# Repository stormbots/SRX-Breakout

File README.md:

# Talon SRX Breakouts
Breakout circuit boards for easier wiring with the Talon SRX motor controller.

All source files are created using [CADSoft Eagle](http://www.cadsoftusa.com/download-eagle/). They can be uploaded by downloading the BRD files, and uploading them to a PCB fabrication service such as [OSHPark.com](http://oshpark.com)

- [SRX Dataport Breakout](SRX_Dataport_Breakout/): Provides a simple breakout to 0.1" servo headers for simpler wiring of inputs
   
- [SRX CAN Plugboard](SRX_CAN_Plugboard/): Provides a spring plug for the SRX for connecting to the CAN network, similar to the other 2015 control system devices.

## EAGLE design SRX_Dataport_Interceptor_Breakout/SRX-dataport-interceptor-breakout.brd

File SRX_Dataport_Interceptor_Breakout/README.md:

# Talon SRX Dataport Intercepter Breakout
This board breaks out the Talon SRX pins into a more easily usable 3-wire configuration that's compatible with standard servo cabling. This variant also includes a passthrough to the Gadgeteer port, allowing mixed usage of both 3 wire and Gadgeteer plug devices from [CTRE](http://www.ctr-electronics.com/). 

For additional configuration of the Talon SRX to take advantage of this board, see the [Talon SRX User's guide](http://content.vexrobotics.com/vexpro/pdf/Talon-SRX-User-Guide-20150201.pdf)

## Wiring
 The 4 3-wire connectors simply match servo cable order. Since switches generally don't care about voltage, all 3-wire signals use 3.3V. The voltage for the Analog Input Signal pin MUST be 3.3V in order to avoid damage to the Talon SRX.
 
 Connection Name | Pin 1 | Pin 2 | Pin 3 
 ---|---|---|---
Forward Limit Switch | GND |3.3V| Signal
Reverse Limit Switch | GND |3.3V| Signal
Quadrature Index Switch | GND |3.3V| Signal
Analog Input | GND |3.3V| Signal

The 4 wire quadrature encoder has a slightly different configuration. In addition, a solder jumper on the reverse side of the board allows for a configurable voltage. This is needed since some encoder boards require 5V signals, rather than the 3.3V.

Connection Name | Pin 1 | Pin 2 | Pin 3 |Pin 4
---|---|---|---|---
 Quadrature Encoder |GND | 3.3V or 5V |Signal A | Signal B

### Gadgeteer Pin Usage Chart
The Gadgeteer passthrough port works exactly as the one on the SRX does, with the same pinout and shroud orientation. 
Note, that compatibility issues will arise if both the Gadgeteer device and 3 wire device try to drive the same input line. This is called [bus contention](https://google.com/search?q=bus contention) and can result in incorrect operation or damage to your devices. 

This is not guaranteed to be complete, but may help assess what pins are available in combination with various other devices

Component                   |Analog |Fwd Limit| Rev Limit |Quad A | Quad B|
----------------------------|:-----:|:-------:|:---------:|:-----:|:-----:|
[CTRE Mag Encoder](http://www.ctr-electronics.com/srx-magnetic-encoder.html) |   Used   |         |           |  Used    |   Used   

[mag]: ""

## Bill Of Materials

Quantity | Description                  | Part Number |link
--------:|-----|------------------------|-------------|---
4        |  3-pin 0.1" header | Generic | [Digikey](http://www.digikey.com/product-detail/en/61300311121/732-5316-ND/4846825)
1        |  4-pin 0.1" header | Generic | [Digikey](http://www.digikey.com/product-detail/en/M20-9990445/952-2265-ND/3728229)
1        |  14-position 0.5" header | FCI 20021321-00014T4LF | [Digikey](https://www.digikey.com/product-detail/en/20021321-00014T4LF/609-3771-ND/2209082)
2        |  10k resistor (0603 package) | Generic | [Digikey](https://www.digikey.com/product-detail/en/RC0603JR-0710KL/311-10KGRCT-ND/729647)
2        |  Jumper wires | Generic 22 gauge wire  | 
1        | 10 pin 0.05" pitch shrouded socket | CNC Tech 3220-10-0100-00| [Digikey](http://www.digikey.com/product-detail/en/3220-10-0100-00/1175-1627-ND/3883661) 

## Assembly
1. Assemble the surface mount components to the bottom of the board
2. Solder the jumper to select the voltage for the quadrature encoder. 
3. Attach the wire jumpers. These jumpers only work as spacers between the Talon SRX and the PCB. This helps stabilize the connector, and prevent shorting against the 0.1" headers.
4. Attach the 0.1" headers so they face away from the body of the Talon SRX
4. Optionally, attach the 0.05" header so they face away from the body of the Talon SRX
5. Place a piece of electrical tape over the bottom of the board, covering the 0.1" headers, resistors, and solder jumpers.

## Mounting 
1. Remove the screws on the Talon SRX
2. Gently connect the backside connector to the Talon SRX. 
3. Re-insert the screws, and tighten gently. Do not use excessive force*

*  _Using significant force on the screws can damage the Talon SRX. It can also cause the 0.1" joints to punch through the electrical tape, causing signal errors or power shorting. The jumper wires will help provide spacing to prevent these issues._

## FRC Technicalities
This is a passive wiring board, and contains no active components.

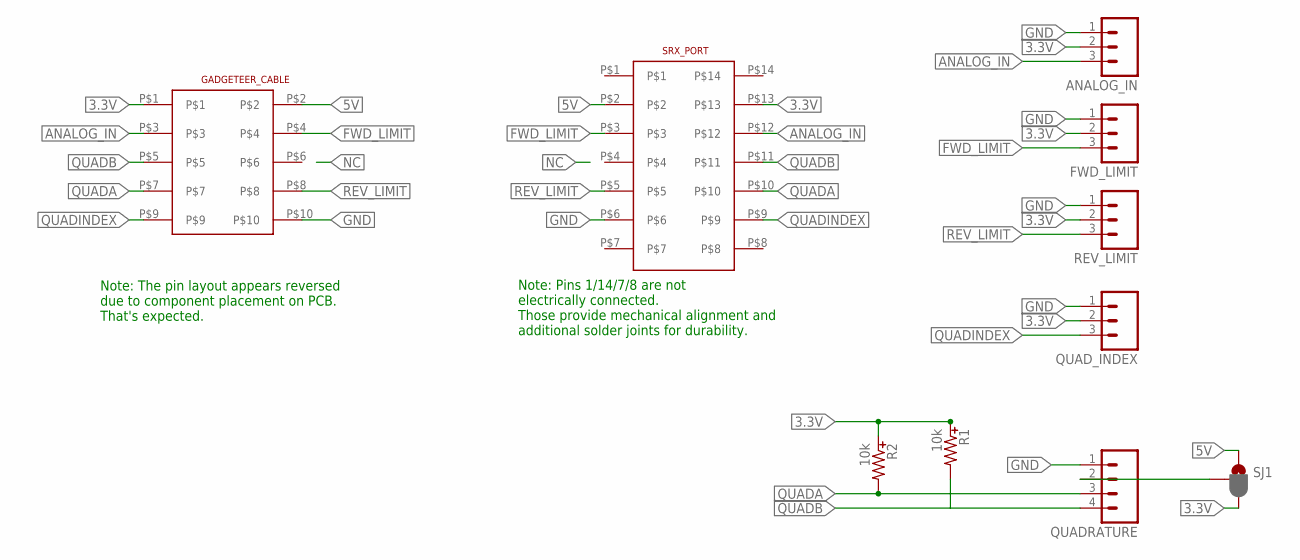
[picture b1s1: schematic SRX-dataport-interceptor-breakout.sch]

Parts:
ANALOG_IN: M03LOCK; 1X03_LOCK
FWD_LIMIT: M03LOCK; 1X03_LOCK
GADGETEER_CABLE: M05X02M_SHROUDED; M2X05_M_SHROUDED
QUADRATURE: M04LOCK; 1X04_LOCK
QUAD_INDEX: M03LOCK; 1X03_LOCK
R1, R2: 10k; 0402-0603-0805-UNIVERSAL
REV_LIMIT: M03LOCK; 1X03_LOCK
SJ1: JUMPER-PAD-3-2OF3_NC_BY_PASTE; PAD-JUMPER-3-2OF3_NC_BY_PASTE_YES_SILK_FULL_BOX
SRX_PORT: M07X0220021321-00014TFLF; M2X07_SMD

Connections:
3.3V: ANALOG_IN.2, FWD_LIMIT.2, GADGETEER_CABLE.P$1, QUAD_INDEX.2, R1.+ (1), R2.+ (1), REV_LIMIT.2, SJ1.3, SRX_PORT.P$13
5V: GADGETEER_CABLE.P$2, SJ1.1, SRX_PORT.P$2
ANALOG_IN: ANALOG_IN.3, GADGETEER_CABLE.P$3, SRX_PORT.P$12
FWD_LIMIT: FWD_LIMIT.3, GADGETEER_CABLE.P$4, SRX_PORT.P$3
GND: ANALOG_IN.1, FWD_LIMIT.1, GADGETEER_CABLE.P$10, QUADRATURE.1, QUAD_INDEX.1, REV_LIMIT.1, SRX_PORT.P$6
QUADA: GADGETEER_CABLE.P$7, QUADRATURE.3, R2.- (2), SRX_PORT.P$10
QUADB: GADGETEER_CABLE.P$5, QUADRATURE.4, R1.- (2), SRX_PORT.P$11
QUADINDEX: GADGETEER_CABLE.P$9, QUAD_INDEX.3, SRX_PORT.P$9
QUAD_VOLTAGE: QUADRATURE.2, SJ1.2
REV_LIMIT: GADGETEER_CABLE.P$8, REV_LIMIT.3, SRX_PORT.P$5

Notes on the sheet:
Note: Pins 1/14/7/8 are not electrically connected. Those provide mechanical alignment and additional solder joints for durability.
Note: The pin layout appears reversed due to component placement on PCB. That's expected.

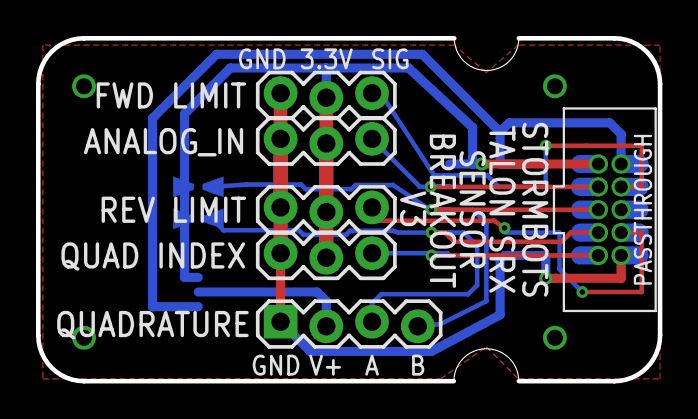
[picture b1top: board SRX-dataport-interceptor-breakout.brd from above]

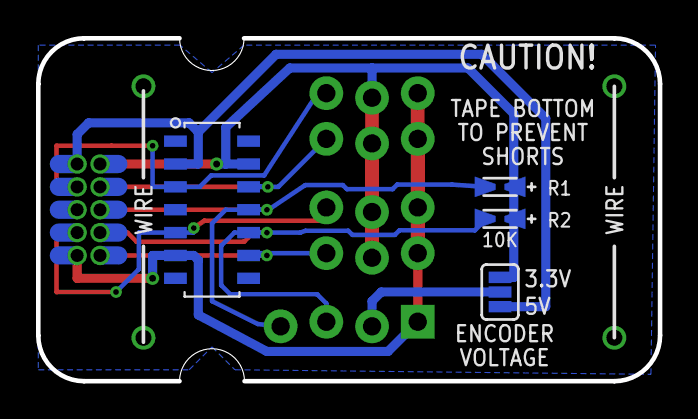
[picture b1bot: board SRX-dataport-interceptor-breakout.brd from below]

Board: 2 copper layers, 34.5 x 19.1 mm, 11 parts (4 on the bottom side), 10 nets.

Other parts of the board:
U$1: TALONSRX

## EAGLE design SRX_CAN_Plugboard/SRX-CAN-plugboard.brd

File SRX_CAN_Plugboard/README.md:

# SRX CAN Plugboard
Provides a spring plug for the SRX for connecting to the CAN network, similar to the other 2015 control system devices. This enables you to cut the wires shorter, and use Ferrule terminators instead of splicing.

## Assembly
No special notes. Simply solder components to the board. 

## Mounting
Can be mounted with either screws or zip ties. Mounting holes and zip tie indents are spaced 1" apart on either side of the connector.

This cannot be mounted directly on conductive surfaces. Doing so will likely short the CAN connections, halting the robot. It's suggested to add a wood block or other spacer when mounting on a surface that may cause the pins to short.

## FRC Technicalities
This is a passive wiring board, and contains no active components.

## Bill Of Materials
Quantity | Description                  | Part Number |link
--------:|-----|------------------------|-------------|---
4        |  2 slot vertical spring mount| Weidmuller 1825960000 | [Digikey](http://www.digikey.com/product-detail/en/1825960000/281-2124-ND/1094462)

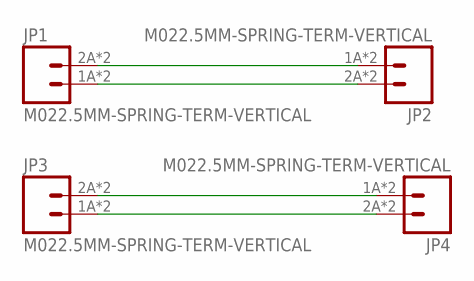
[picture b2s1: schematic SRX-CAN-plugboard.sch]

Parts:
JP1, JP2, JP3, JP4: M022.5MM-SPRING-TERM-VERTICAL; 1824740000-2X-VERTICAL-SPRING-TERMINAL

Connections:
unnamed: JP3.2A (2), JP3.2B (2), JP4.1A (1), JP4.1B (1)
unnamed: JP3.1A (1), JP3.1B (1), JP4.2A (2), JP4.2B (2)
unnamed: JP1.1A (1), JP1.1B (1), JP2.2A (2), JP2.2B (2)
unnamed: JP1.2A (2), JP1.2B (2), JP2.1A (1), JP2.1B (1)

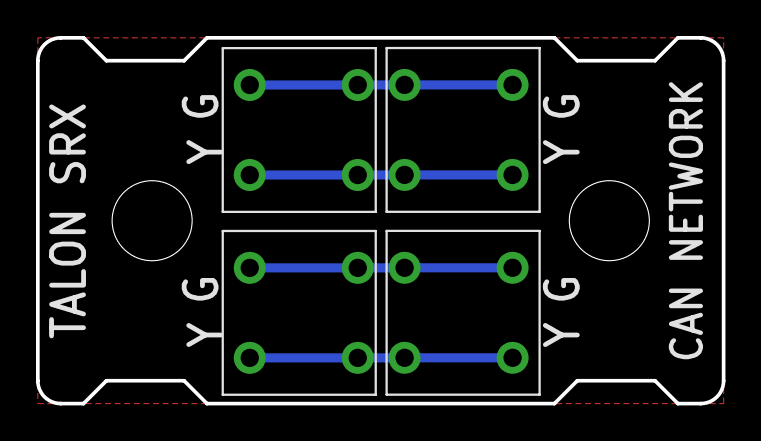
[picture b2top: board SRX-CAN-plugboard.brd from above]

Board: 2 copper layers, 38.1 x 20.3 mm, 4 parts (0 on the bottom side), 4 nets.

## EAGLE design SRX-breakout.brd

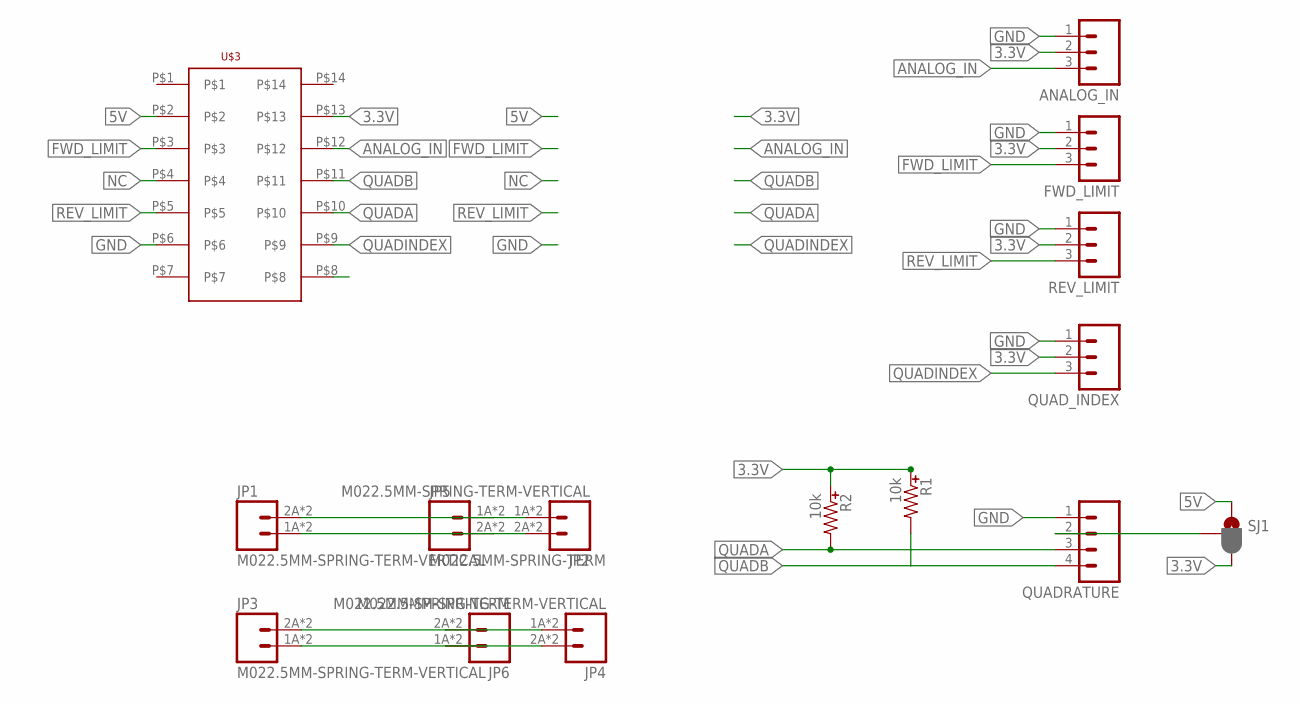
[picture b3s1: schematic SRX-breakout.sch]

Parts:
ANALOG_IN: M03LOCK; 1X03_LOCK
FWD_LIMIT: M03LOCK; 1X03_LOCK
JP1, JP2, JP3, JP4: M022.5MM-SPRING-TERM-VERTICAL; 1824740000-2X-VERTICAL-SPRING-TERMINAL
JP5, JP6: M022.5MM-SPRING-TERM; 1824740000-2X-STRAIGHT-SPRING-TERMINAL
QUADRATURE: M04LOCK; 1X04_LOCK
QUAD_INDEX: M03LOCK; 1X03_LOCK
R1, R2: 10k; 0402-0603-0805-UNIVERSAL
REV_LIMIT: M03LOCK; 1X03_LOCK
SJ1: JUMPER-PAD-3-2OF3_NC_BY_PASTE; PAD-JUMPER-3-2OF3_NC_BY_PASTE_YES_SILK_FULL_BOX
U$3: M07X0220021321-00014TFLF; M2X07_SMD

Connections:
3.3V: ANALOG_IN.2, FWD_LIMIT.2, QUAD_INDEX.2, R1.+ (1), R2.+ (1), REV_LIMIT.2, SJ1.3, U$3.P$13
5V: SJ1.1, U$3.P$2
ANALOG_IN: ANALOG_IN.3, U$3.P$12
FWD_LIMIT: FWD_LIMIT.3, U$3.P$3
GND: ANALOG_IN.1, FWD_LIMIT.1, QUADRATURE.1, QUAD_INDEX.1, REV_LIMIT.1, U$3.P$6
unnamed: JP3.2A (2), JP3.2B (2), JP4.1A (1), JP4.1B (1), JP6.2A (1), JP6.2B (1)
unnamed: JP3.1A (1), JP3.1B (1), JP4.2A (2), JP4.2B (2), JP6.1A (2), JP6.1B (2)
unnamed: JP1.1A (1), JP1.1B (1), JP2.2A (2), JP2.2B (2), JP5.2A (1), JP5.2B (1)
unnamed: JP1.2A (2), JP1.2B (2), JP2.1A (1), JP2.1B (1), JP5.1A (2), JP5.1B (2)
NC: U$3.P$4
QUADA: QUADRATURE.3, R2.- (2), U$3.P$10
QUADB: QUADRATURE.4, R1.- (2), U$3.P$11
QUADINDEX: QUAD_INDEX.3, U$3.P$9
QUAD_VOLTAGE: QUADRATURE.2, SJ1.2
REV_LIMIT: REV_LIMIT.3, U$3.P$5

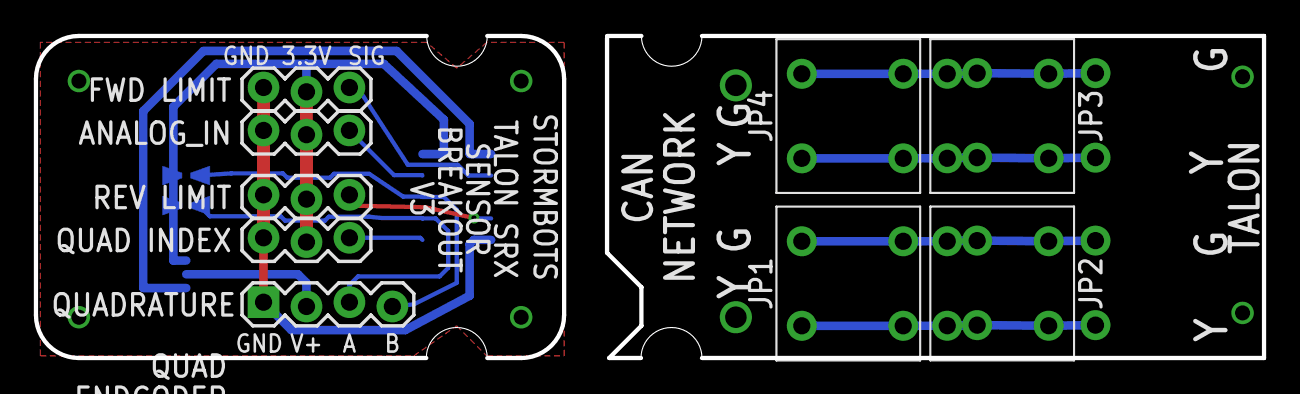
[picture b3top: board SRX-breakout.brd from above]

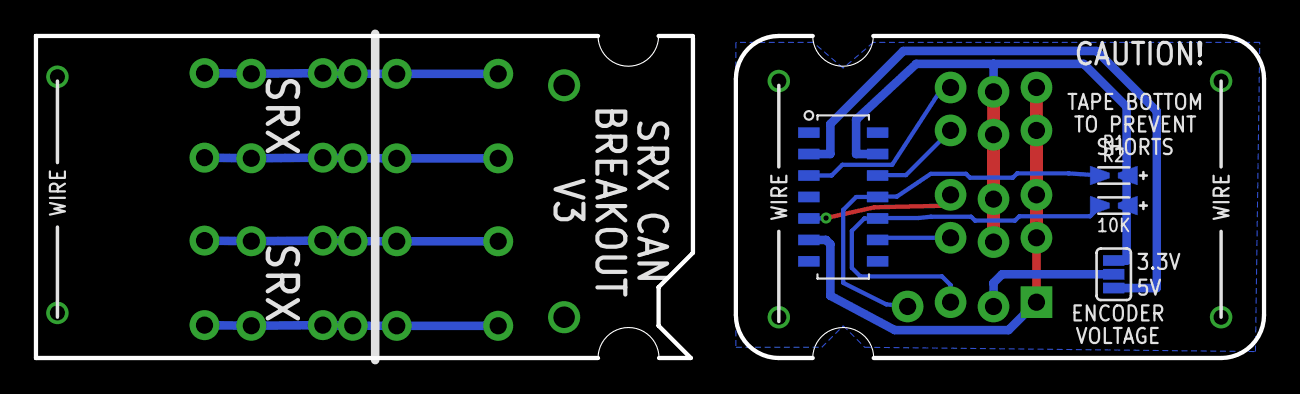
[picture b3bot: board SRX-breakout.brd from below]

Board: 2 copper layers, 72.6 x 19.1 mm, 16 parts (4 on the bottom side), 14 nets.

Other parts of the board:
U$1: TALONSRX

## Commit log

2015-11-09 Init with V2 boards
2015-11-09 Updated mechanical drawing of SRX
2015-11-09 Add CAN subboard
2015-11-22 Minor adjustments for mechanical purposes
2016-01-06 Add documentation
2016-01-14 Wrong part number
2016-02-18 Add SRX breakout with passthrough
2016-02-18 Fixed text to represent the correct board
2016-11-21 Markdown formatting error
2016-11-21 Markdown Format errors

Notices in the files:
parts and their libraries:
SparkFun-Connectors: Licensing: Creative Commons ShareAlike 4.0 International - https://creativecommons.org/licenses/by-sa/4.0
